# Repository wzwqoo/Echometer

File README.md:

# Echometer

A pocket-sized, battery-powered **ultrasonic bat detector**. It listens for
bat calls above 19 kHz, and when it hears one it records a 3.84-second
full-spectrum clip at **256 ksps** into PSRAM and serves it over its own Wi-Fi
network. Open a phone browser, download the WAV, and import it straight into
the Wildlife Acoustics **Echo Meter** app — the files carry GUANO metadata and
are accepted as Echo Meter Touch 2 Pro recordings.

No SD card, no cables, no custom phone app, no laptop in a field at midnight.

This is **v4**, the fourth board in the series. It is the first one that is
genuinely portable and the first one that doesn't clip on a close bat: the
analog front end has **six switchable gain steps from 22× to 782×**, chosen
from the web page or tracked automatically, and the whole thing runs off a
protected LiPo with charger and boost on board. See
[Design history](#design-history) for how it got here.

|  |  |
|:--:|:--:|
|  |  |
| **Japanese Pipistrelle**<br>*Alionoctula abramus* &mdash; recorded by this board, opened in the Echo Meter app | **Least Horseshoe Bat**<br>*Rhinolophus pusillus* &mdash; the ~108 kHz caller that set the sample rate |

---

## Contents

- [Specifications](#specifications)
- [How it works](#how-it-works)
- [Repository layout](#repository-layout)
- [Getting started](#getting-started)
- [Using it](#using-it)
- [Hardware in brief](#hardware-in-brief)
  - [Switchable gain](#switchable-gain)
  - [Power](#power)
  - [Pinout](#pinout)
- [Firmware in brief](#firmware-in-brief)
- [Errata — read before ordering the PCB](#errata--read-before-ordering-the-pcb)
- [Design history](#design-history)
- [Roadmap](#roadmap)
- [References](#references)

---

## Specifications

| | |
|---|---|
| Detection band | 19 – 128 kHz |
| Sampling | 256 ksps, 12-bit, external SAR ADC (ADCS7476) |
| Frequency resolution | 125 Hz/bin (2048-point FFT, 8 ms frames) |
| Analog gain | 6 steps, **22× – 782×** (26.9 – 57.9 dB), manual or AGC |
| Microphone | Knowles SPU0410LR5H-QB MEMS, −38 dBV/Pa, usable to ≈ 80 kHz |
| Clip length | 3.84 s (983 040 samples, 1.97 MB) |
| Clip storage | up to 8 PSRAM slots — 4 on an 8 MB module; RAM-only, lost at power-off |
| Transfer | open Wi-Fi AP `echometer` → `http://192.168.4.1` |
| File format | 16-bit mono WAV + GUANO chunk, `CHIRP_YYYYMMDD_HHMMSS.wav` |
| Compute | ESP32-S3 DevKitC-1, octal PSRAM, ESP-IDF ≥ 5.2 |
| Power | 2000 mAh LiPo, TP4056 charger @ 1 A, DW01/FS8205A protection, MT3608 boost |
| PCB | 4-layer, KiCad 10, gerbers in [`hardware/fab/`](hardware/fab/) |

## How it works

```text
                        ┌── 74HC4053 mux ──┐
                        │  (3 × GPIO)      │
                        ▼                  ▼
  ┌────────┐      ┌───────────┐      ┌──────────┐      ┌───────────┐
  │ conical│      │  OPA838   │      │  TL972   │      │ ADCS7476  │
──│  horn  │─────▶│  ×4.25/34 │─────▶│ ×5.2…23  │─────▶│ 12-bit    │
  │        │ MEMS │  stage 1  │  HP  │ stage 2  │  AA  │ 256 ksps  │
  └────────┘  mic └───────────┘      └──────────┘      └─────┬─────┘
                                                             │ I²S RX DMA
                                                             ▼
   Safari ◀── HTTP ◀── SoftAP ◀── PSRAM clip ◀── trigger ◀── 2048-pt FFT
     │                             4 × 3.84 s      >19 kHz    (esp-dsp)
     ▼                                             narrowband
  Echo Meter app                                   3 frames
```

1. Press **BOOT** to arm. The LED flashes green whenever ultrasound is present.
2. Every 2048-sample buffer is FFT'd. A detection needs a **narrowband** peak
   above 19 kHz that **persists** across 3 consecutive frames — broadband
   transients (a finger on the board, contact noise) are rejected.
3. On detection the clip streams into a PSRAM slot for 3.84 s. The LED goes
   completely silent during the write — its own drive current used to print
   evenly-spaced clicks into the spectrogram.
4. Blue flash when saved, then back to idle. Join Wi-Fi `echometer`, browse to
   `http://192.168.4.1`, download or delete clips, and set the gain.

The interesting trick is the ADC clocking. The ESP32-S3's internal ADC-DMA path
tops out near 83 ksps, nowhere near enough for a bat. So an external SAR ADC is
driven by the **I²S peripheral pretending to be an SPI master**: in 16-bit
stereo master mode the WS line toggles every 16 bit-clocks, so WS becomes the
ADC's `CS#` and BCK its `SCLK`. RX DMA captures every sample with zero
per-sample CPU, jitter-free, at an 8.192 MHz bit clock.

## Repository layout

| Path | Contents |
|---|---|
| [`hardware/`](hardware/) | KiCad 10 project — schematic, 4-layer PCB, gerbers, BOM, horn generator. See [hardware/README.md](hardware/README.md) for the analog design. |
| [`firmware/`](firmware/) | ESP-IDF application. See [firmware/README.md](firmware/README.md) for the detection logic and bring-up lessons. |
| [`firmware/main/archive/`](firmware/main/archive/) | Earlier firmware variants kept for reference — v3's original, an SD-card recorder, a board bring-up test. |
| [`docs/img/`](docs/img/) | Photographs and screenshots used in this README. |

## Getting started

**You need:** an ESP32-S3-DevKitC-1 with **octal** PSRAM, the assembled v4
board, a 2000 mAh LiPo with a JST-PH lead, and ESP-IDF ≥ 5.2.

```bash
cd firmware
. ~/software/esp-idf/export.sh              # adjust to your ESP-IDF path
idf.py build
idf.py -p /dev/ttyUSB0 flash monitor        # the COM (UART) USB-C port
```

The DevKitC-1 has two USB-C ports. **COM** (CP2102N → UART0) does flashing and
the log console and always works. If a bad flash ever bricks the app: hold
BOOT, tap RESET, release → ROM download mode, reflash over COM.

Before you build the board, read
[Errata](#errata--read-before-ordering-the-pcb) — item 1 is blocking.

## Using it

| Action | What happens |
|---|---|
| Press BOOT | Arm. LED flashes green while ultrasound is present. |
| Detection | LED silent, 3.84 s clip written to PSRAM, then blue flash. |
| Press BOOT while armed | Disarm back to idle. Presses during a write are ignored. |
| Join `echometer` (open network) | AP is up in every state. |
| `http://192.168.4.1` | Clip list, newest first: download, delete, set gain, toggle AGC. |

Clips live in RAM only — **they are lost at power-off**. Download before you
disconnect the battery.

To get a clip into the Echo Meter app on iOS: download in Safari, then
Files → share sheet → *Copy to Echo Meter*.

---

## Hardware in brief

Everything below is the summary. Full derivations — op-amp selection, mic
specs, the input common-mode budget, every filter corner, the power design,
the pinout, the acoustic horn and the bat call-level budgets — are in
[hardware/README.md](hardware/README.md).

Single channel, single 3.3 V analog rail, everything biased to mid-rail
(VREF ≈ 1.65 V). Stage 1 is a **TI OPA838** — 300 MHz GBW, decompensated,
1.8 nV/√Hz — because gain × 120 kHz has to fit inside the gain-bandwidth
product. Stage 2 is a **TI TL972**, rail-to-rail in and out, which drives the
ADC to full swing on 3.3 V. Both stages are non-inverting with a 1 kΩ leg to
VREF. The band is ≈ 19 kHz – 128 kHz: two 10 nF high-passes stacked at the
bottom, a 72 kHz RC anti-alias filter ahead of the ADC at the top.

### Switchable gain

A **74HC4053** analog mux switches extra feedback resistors **in parallel**
with a permanent one at each stage's summing node — one switch on stage 1, two
on stage 2. Parallel resistors *lower* the gain, the permanent resistors mean
the loop is never open, and the mux's Y0-when-LOW polarity means the state the
ESP32's GPIOs sit in at reset is **minimum gain, which cannot clip**.

| **Total** | dB | Clips near | Use |
|---|---|---|---|
| **22×** | 26.9 | 105 dB SPL | cave / roost, bats at arm's length |
| **51×** | 34.2 | 98 dB SPL | |
| **98×** | 39.8 | 92 dB SPL | general close work |
| **210×** | 46.4 | 86 dB SPL | default at cold boot |
| **408×** | 52.2 | 80 dB SPL | |
| **782×** | 57.9 | 74 dB SPL | distant passes, ~30 m |

Steps are 5.6–7.3 dB apart. "Clips near" is the input SPL at which the TL972
output hits its rail. The range stops at 782× because past ~800× you are
amplifying the microphone's own noise rather than signal — further reach has to
come from narrowband processing, not from the front end.

Resistor values, the switch-state table, why the three switches are split 1/2
across the stages, and why the switches sit at the summing node:
[hardware/README.md](hardware/README.md#gain--how-the-switching-works).

### Power

USB charger → cell → protection → boost to 5.31 V for the module, with the
analog rail taken off separately. The one decision worth naming here: **the
analog LDO is fed from the battery, not from the boost.** The TPS74801's
separate BIAS pin runs its control loop from +5 V so the pass FET can be driven
above VIN, which lets IN sit at the raw cell voltage. The win isn't efficiency,
it's noise — the analog rail never sees the MT3608's 1.2 MHz ripple, which no
LDO's PSRR is good at rejecting.

Two things to know before you use it:

- **Charging while running works**, but the load current means the TP4056 may
  never reach its termination threshold, so it can sit in CV at 4.2 V and the
  green LED may never come on. Don't leave it plugged in for days.
- **There is no power switch.** The board runs from the moment the cell is
  connected — unplug J6 to stop it. See errata 5 to store it charged.

Rail diagram, component values, the 5.31 V boost-margin calculation and where
to add a switch if you want one: [hardware/README.md](hardware/README.md#power).

### Pinout

ADC on GPIO 4 / 5 / 6 (I²S WS / BCK / DIN), gain select on GPIO 38 / 37 / 36
(⚠ **see errata 1**), RGB LED on 48, BOOT button on 0. Full header-pin table:
[hardware/README.md](hardware/README.md#pinout--esp32-s3-devkitc-1).

---

## Firmware in brief

ESP-IDF application, single `main.c`. Full detail — state machine, WAV/GUANO
construction, sdkconfig requirements and the bring-up lessons — is in
[firmware/README.md](firmware/README.md).

| State | Entered by | LED |
|---|---|---|
| IDLE | boot / disarm | off |
| DETECT | BOOT press | green flash while ultrasound present |
| RECORD | detection persists 3 frames | **silent** for the 3.84 s write |
| after RECORD | write finished | blue flash ~1.2 s → IDLE |

**Detection.** 2048-point real FFT per buffer via esp-dsp. Trigger requires, on
3 consecutive buffers: a bin above 19 kHz (bin ≥ 152) over
`ULTRASONIC_THRESH_COUNTS`, **and** a peak ≥ 20× the average power of the rest
of the >19 kHz band. The tonality test is what rejects broadband impulses; the
persistence test is what rejects momentary ones.

**Gain control.**

- **Web:** `http://192.168.4.1` → tap a gain. Picking one by hand turns the AGC
  off, and the choice is saved to NVS so it survives a power cycle.
- **AGC:** fast attack, slow decay. Any frame peaking above 90 % of full scale
  drops the gain one step immediately; the gain only steps back up after ~1 s
  (120 frames) below 10 %. Asymmetric on purpose — clipping happens in the
  **analog** domain before the ADC, so a clipped call is unrecoverable, while a
  symmetric AGC would pump on every gap between calls.
- **Frozen during RECORD.** A gain step mid-clip would put a discontinuity in
  the waveform and make the clip useless for absolute amplitude. The gain in
  force is latched at trigger time and written into the clip's GUANO metadata
  (`Note` plus `Echometer|Gain`), so SPL can be reconstructed offline.
- After every gain change the detector skips 2 frames while the mux's charge
  injection settles out of the summing node, so a switch is never mistaken for
  a call.

**HTTP endpoints:** `/` (clip list), `/dl`, `/del`, `/gain?i=N`, `/agc?on=0|1`.

**A note on the device identity in the metadata.** The Echo Meter app validates
the GUANO `Model` field against known Wildlife Acoustics modules and rejects
anything else, so the firmware writes `Model: Echo Meter Touch 2 Pro` — a
format this recorder genuinely matches (256 kHz, 16-bit, full-spectrum mono).
True provenance is kept in the GUANO `Note` field. Keep that in mind before
sharing files anywhere that trusts the device tag.

---

## Errata — read before ordering the PCB

Known problems with the v4 board as drawn. **Item 1 is blocking** — fix it in
the schematic before you send gerbers. The rest are things to know before you
build, not stop-ships.

**1. Two gain-select signals land on the octal-PSRAM bus.** With
`CONFIG_SPIRAM_MODE_OCT=y`, GPIO35/36/37 belong to the PSRAM controller and
cannot be used for anything else, but the PCB routes Gain S2 to J12.11
(GPIO37) and Gain S3 to J12.12 (GPIO36). The firmware already assumes the
corrected pins — `PIN_GAIN_S1/S2/S3` are GPIO 38/39/40 — so an uncorrected
board will not switch gain.
**Fix:** move S2 to J12.9 (GPIO39) and S3 to J12.8 (GPIO40). GPIO39/40 are
MTCK/MTDO, free here only because the DevKitC-1 debugs over the built-in
USB-Serial-JTAG on GPIO19/20. See
[firmware/README.md](firmware/README.md#5-gpio-choice-is-constrained-by-psram-mode).

**2. Stage 1's lowest gain step sits below the OPA838's minimum stable gain.**
The OPA838 is decompensated, with a minimum stable gain of +7; stage 1's low
setting is 4.25. The design relies on C14 (27 pF across R13) to provide the
compensation the topology needs, and 27 pF is small enough that stray
capacitance matters. If the three low gain steps ring, peak or oscillate,
this is the first place to look.

**3. The +5 V rail has ~390 mV of bias margin, and it needs verifying.** The
boost is set to 5.31 V because the TPS74801's BIAS pin must stay at least
1.62 V above the 3.3 V output, i.e. ≥ 4.92 V. Measure the sag on a real board:
if +5 V dips below 4.92 V during a Wi-Fi TX burst, the LDO loses bias headroom
and the analog rail glitches during exactly the moments you transmit.

**4. The SD footprint (J5) is +5 V and unbuffered.** Pin 5 is fed +5 V and the
SPI lines are not level-shifted, so J5 accepts an SD **module** with its own
regulator and level shifters — never a bare card socket. The current firmware
does not use it; leave it unpopulated unless you are building the archived
recorder.

**5. There is no power switch, and the cell will over-discharge in storage.**
The boost's EN is tied to its own input, so the board runs from the moment the
cell is connected. Standby drain as built is 50–120 mA, which flattens
2000 mAh in 17–40 hours and then parks the cell at the DW01's 2.4 V cutoff —
bad for lithium.
**Fix:** unplug J6 for storage and store the cell charged. If you add a switch,
put it in the `Lipo+ → L1 / U8.5` branch, **not** on the boost's EN pin — the
MT3608 is asynchronous, so `Lipo+ → L1 → D3 → +5V` is a permanent DC path that
survives disabling the boost. See
[hardware/README.md](hardware/README.md#charging-and-switching-both-with-caveats).

**6. Several schematic symbols carry stale part numbers.** R13, R23/R25, R24
and R26 inherit a 24 kΩ `Part#` / `LCSC Part #` from their previous value, and
C16 inherits a 10 nF one. Those fields are cleared in the checked-in
[`hardware/v4.csv`](hardware/v4.csv), so **ordering from the CSV is safe** —
but fix the symbol properties before the next `kicad-cli sch export bom`.

---

## Design history

Four boards, each one built to answer the question the previous one raised.

| | v1 | v2 | v3 | v4 |
|---|---|---|---|---|
| **Compute** | STM32F401CBU6 | STM32F446RET6 (Nucleo) | ESP32-S3 | ESP32-S3 |
| **Sampling** | internal ADC, free-running DMA | internal ADC, TIM2-gated **240 ksps** | external ADCS7476 via I²S, **256 ksps** | same |
| **Detection** | none — raw recorder | CMSIS-DSP FFT, >19 kHz threshold | + tonality + persistence | same |
| **Storage** | micro-SD (SPI1, FatFS) | micro-SD (SPI3, FatFS) | 4 × PSRAM slots | up to 8 slots |
| **Retrieval** | pull the card / USB CDC | pull the card / UART + Python | **Wi-Fi + Safari + GUANO WAV** | same |
| **Gain** | analog board, fixed | fixed 121× | fixed 625× | **6 steps, 22×–782× + AGC** |
| **Listening** | heterodyne + FD to a speaker | — | — | — |
| **Power** | 9 V in, LM2574 + LDOs | dev-board USB | USB (browned out) | **LiPo + charger + protection + boost** |

### v1 — does the analog even work?

A custom STM32F401CBU6 mainboard plus a separate analog board carrying the
classic hobbyist bat-detector chain: SPU0410 MEMS mic → LM358 preamp → CD4066
mixer switched by a TLC555 → LM386 → speaker, i.e. **heterodyne and frequency
division straight to your ears**. Two small preamp boards (one OPA838, one
TL972) were spun alongside it to compare op-amps on real signals.

The MCU side ran FreeRTOS with three tasks: ADC1 in continuous DMA into a
double buffer, a ring buffer feeding FatFS on a micro-SD over SPI1, and a
debounced button. Power was 9 V in through an LM2574 buck and NCP718/NCP163
LDOs.

**What it proved:** the microphone, the horn and the amplifier chain all work,
and you can hear bats. **What it cost:** hearing a bat isn't recording one —
the heterodyne path destroys the signal it demodulates. There was no detection
logic at all, so recording was start/stop by hand. The ADC free-ran on a
software start with no timer trigger, so the sample clock had jitter. And
splitting analog and digital across two boards joined by 4-pin headers was an
invitation to pickup.

**→ v2:** drop the speaker path entirely, go full-spectrum digital, put the ADC
on a hardware time base, and add a real FFT detector.

### v2 — detect it, don't just hear it

A Nucleo-F446RE with a custom analog + SD daughterboard: SPU0410 →
**OPA838 → TL972**, single 3.3 V rail, mid-rail bias — the two-stage topology
that survives into v4. TIM2 TRGO gates ADC1 at exactly **240 ksps** into a
2 × 2048 DMA double buffer, and each half-buffer goes through
`arm_rfft_fast_f32` from CMSIS-DSP: 117 Hz/bin, trigger on any bin ≥ 163
(>19 kHz) above 50 counts. Detect and record are two states with different LED
blink rates; recording writes raw `uint16` samples to FatFS over SPI3 with an
`f_sync` every 100 writes. Python tools (`bat_record.py`, `bat_viewer.py`,
`bat_waveform.py`) pull captures over the serial port and plot them.

Gain went from 11× per stage (**121×** total) to 25× per stage (**625×**)
during bring-up. At 121× real calls sat barely above the noise floor; the 5×
jump is what moved detection from marginal to reliable.

**What it cost:** 240 ksps means a 120 kHz Nyquist, and that was the internal
ADC's practical ceiling — the target species here, *Rhinolophus pusillus*, calls
at ~108 kHz, right at the edge. Getting files off meant pulling the card or
dumping over serial. And the gain was still a soldered constant.

**→ v3:** an external ADC fast enough to have real margin above 108 kHz, and a
way to get files onto a phone in the field.

### v3 — fast enough, and wireless

ESP32-S3 with an external **ADCS7476** 12-bit SAR clocked by the I²S
"WS-as-CS" trick at **256 ksps** — zero per-sample CPU, 128 kHz Nyquist.
Detection moved to esp-dsp and gained the two tests that make it usable
outdoors: **tonality** (peak bin ≥ 20× the mean power of the rest of the band)
and **persistence** (3 consecutive frames). Clips go to PSRAM — four 3.84 s
slots in 8 MB — and are served over a SoftAP as WAVs with a **GUANO** metadata
chunk that the Echo Meter iPhone app accepts. Two mics and two full channels,
fixed 625×.

That combination is what made it a real detector: no card, no cable, and a
phone app that already knows how to draw a spectrogram.

**What it cost, and this is the whole reason v4 exists:**

- **625× clipped constantly.** Roughly 9 out of 10 close calls railed the
  second stage, smearing the spectrogram into broadband bars and false
  harmonics. Clipping happens in the analog domain, so no amount of digital
  processing recovers it — and there was no way to turn the gain down.
- **It browned out.** Wi-Fi RF calibration and TX bursts (300–400 mA on top of
  octal PSRAM) tripped the brownout detector on marginal USB supplies. Inline
  USB "noise filter" dongles made it *worse* — series resistance is exactly the
  problem. Downloads, being the heaviest sustained RF load, failed first.
- **A floating ADC input false-triggered on touch.** Fixed in firmware by the
  tonality and persistence tests; the hardware fix was left for the next spin.
- **The LED printed clicks into the spectrogram.** The WS2812's RMT refresh
  coupled into the front end, so the firmware learned to keep it silent for the
  whole capture window.
- **The mic-supply filter did nothing.** 10 Ω + 110 nF corners at 159 kHz —
  above the band it was supposed to clean.

**→ v4:** make the gain adjustable, and stop feeding a 400 mA radio through a
thin cable.

### v4 — portable, and it doesn't clip

| Area | v3 | v4 |
|---|---|---|
| Gain | fixed 625× | **6 steps, 22×–782×**, web-selectable + AGC |
| Gain control | — | 74HC4053 mux at both summing nodes, 3 GPIOs |
| Channels | 2 mics, 2× OPA838 + 2× TL972 | 1 mic, 1× OPA838 + 1× TL972 — gain replaces the second channel |
| Power source | USB only | LiPo 2000 mAh + charger + protection + boost |
| Charging | — | TP4056 @ 1 A, red/green status LEDs |
| Cell protection | — | DW01 + FS8205A, low-side |
| 3V3 analog rail | LDO from 5 V (boost output) | LDO **from the battery**, bias from 5 V |
| Mic supply filter | 10 Ω + 110 nF (159 kHz — did nothing) | **100 Ω + 10 µF (159 Hz)** |
| Anti-alias | 100 Ω + 10 nF (159 kHz, above Nyquist) | **100 Ω + 22 nF (72 kHz)** |
| Wi-Fi burst reservoir | external | **470 µF on board** at the module header |
| Floating ADC input | v3 erratum — false triggers | driven from the op amp through 100 Ω; can't float |
| Clip metadata | timestamp only | **gain recorded in GUANO** |

The trade worth naming: v4 gives up v3's second channel. Two mics at two fixed
gains is the other classic way to get wide dynamic range — digitise both, keep
whichever didn't clip, zero AGC artifacts. One switched channel costs a mux and
some AGC logic but buys 31 dB of range instead of one fixed step, and it frees
the board area that paid for the battery.

## Roadmap

Carried forward, in rough order of value:

- **Ring buffer for pre-trigger audio.** The clip currently starts at the
  triggering buffer, so the calls *before* detection fired are lost. This is
  the single biggest capture upgrade left — every serious passive recorder
  keeps a few seconds of pre-roll.
- **Adaptive trigger.** A running noise-floor estimate (exponential moving
  average of ultrasonic-band energy) rather than the fixed
  `ULTRASONIC_THRESH_COUNTS`. Note that with variable gain a fixed threshold
  now means a *different* absolute sensitivity at each step, which makes this
  more pressing than it was in v3.
- **Call-shape gating.** Require a swept FM component, plausible duration
  (~2–20 ms) and inter-pulse interval, to reject bush-crickets and machinery.
  The tonality + persistence test is a first cut at this.
- **Duty cycling** for unattended overnight runs — light sleep between checks,
  or a low-power always-on trigger path that wakes full recording on a hit.
- **Pause the AP during capture**, so no TX spike or RF pickup can coincide
  with the 3.84 s sampling window.

For reference, AudioMoth uses a plain amplitude threshold; Song Meter /
Kaleidoscope use band-limited energy triggers; Anabat uses zero-crossing
frequency division; and the most advanced run an on-device CNN
(e.g. BatDetect2) to detect and classify in real time.

## References

- [GUANO metadata specification](https://guano-md.org)
- TI [OPA838](https://www.ti.com/lit/gpn/opa838), TL972, ADCS7476, TPS74801 datasheets
- Knowles SPU0410LR5H-QB datasheet and Ultrasonic Application Note AN17
- [AudioMoth](https://www.openacousticdevices.info/) — reference low-power design
- [BatDetect2](https://github.com/macaodha/batdetect2) — CNN call detection and classification

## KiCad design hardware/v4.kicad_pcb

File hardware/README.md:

# Hardware — analog front end, power, PCB and acoustics

KiCad 10 project (`v4.kicad_pro`, schematic + 4-layer PCB), fabrication outputs
in [`fab/`](fab/), BOM in [`v4.csv`](v4.csv), and the parametric acoustic-horn
generator [`ultrasonic_horn_freecad.py`](ultrasonic_horn_freecad.py).

The schematic is split over two sheets: `v4.kicad_sch` (root) and
`MCU.kicad_sch` (everything — front end, ADC, power, module headers).

> Read the errata in the [top-level README](../README.md#errata--read-before-ordering-the-pcb)
> before ordering. Item 1 is blocking: two of the three gain-select signals land
> on the octal-PSRAM bus and must be moved.

---

## Analog front end

### Transducer

**Knowles SPU0410LR5H-QB**, one fitted. An analog MEMS mic with usable response
through the target bat band; its raw output is small — tens of millivolts for a
loud, close call — so it must be amplified and biased into the ADC's input
range before sampling.

| Parameter | Value |
|---|---|
| Type | analog MEMS (SiSonic), bottom-port, omnidirectional |
| Sensitivity | −38 dBV/Pa (±3 dB) ≈ 12.6 mV/Pa @ 94 dB SPL, 1 kHz |
| SNR | 63 dB(A) → self-noise ≈ 31 dB(A) SPL |
| Frequency response | ~100 Hz → usable to ≈ 80 kHz (rising resonance ~20–25 kHz) |
| Max acoustic input | ≈ 120 dB SPL |
| Supply / current | 1.5–3.6 V / ~123 µA |
| Output impedance | ~200 Ω |
| Package | 3.76 × 2.95 × 1.10 mm, 0.25 mm port |

The 0.25 mm acoustic port sits at the throat of the conical horn.

### Op-amp choice

The amplifier must pass the full ultrasonic band **and** apply large gain
without rolling off, which sets a hard requirement on gain–bandwidth product:
`GBW ≥ gain × 120 kHz`. Two devices:

| Stage | Part | Why |
|---|---|---|
| 1st gain | **TI OPA838** (OPA838IDBVR) | 300 MHz GBW, decompensated (min stable gain +7), 1.8 nV/√Hz, ~1 mA |
| 2nd gain / ADC driver | **TI TL972** (TL972IDR) | dual rail-to-rail I/O, 12 MHz GBW — drives the ADC to full swing on 3.3 V |

Both run single-supply and bias the signal to **mid-rail (VREF ≈ 1.65 V)** so
the AC waveform swings symmetrically inside the ADC's 0–3.3 V window. A **TI
TPS74801** low-noise LDO supplies the analog rail and VREF, so digital
switching noise doesn't couple into the µV-level mic signal.

Note the OPA838's decompensation: its minimum stable gain is +7, which is a
real constraint on the gain-step table below — stage 1's low setting of 4.25
would be unstable on its own, and is only usable because C14 (27 pF across
R13) provides the compensation the topology needs.

### Gain — how the switching works

Both stages are non-inverting with a 1 kΩ leg to VREF. Each has a
**permanent** feedback resistor, and a **74HC4053** analog mux switches further
resistors in **parallel** with it, which *lowers* the gain.

| Stage | Amp | Rg | Permanent Rf | Switched in parallel | Gains |
|---|---|---|---|---|---|
| 1 | OPA838 (U3) | R6 = 1 k | R13 = 33 k | R26 = 3k6 via switch 1 | 34 / 4.25 |
| 2 | TL972B (U2) | R12 = 1 k | R25 = 22 k | R23 = 22 k (sw 2), R24 = 6k8 (sw 3) | 23 / 12 / 6.2 / 5.2 |

Three design decisions are load-bearing here:

**The permanent resistors are never switched out.** The loop is closed in every
mux state, including the ~300 ms before firmware runs and the instant the mux
transitions. Nothing can rail.

**The polarity is chosen so reset means quiet.** The 4053 selects Y0 — resistor
connected, parallel combination, *lower* gain — when its select pin is **LOW**.
GPIOs sit low at reset, so the board wakes at minimum gain, which cannot clip.

**The switches sit at the summing node**, mux common to the op-amp inverting
input and the resistors to Y0. Both sides of a closed switch are therefore at
virtual ground, so the mux's on-resistance sees an almost constant voltage.
That is what keeps the 4053's on-resistance nonlinearity out of the signal —
put the switch anywhere the voltage swings and it becomes a distortion source.

**Why the switches are split 1 / 2 across the stages.** Switching resistors in
parallel adds conductances, so the achievable ratio within one stage is bounded
— a single stage can only span about 18 dB however you pick the values. Two
stages multiply, giving the full 31 dB.

### The six steps

| S1 | S2 | S3 | Stage 1 | Stage 2 | **Total** | dB | Clips near |
|---|---|---|---|---|---|---|---|
| 0 | 0 | 0 | 4.25 | 5.2 | **22×** | 26.9 | 105 dB SPL |
| 0 | 0 | 1 | 4.25 | 12 | **51×** | 34.2 | 98 dB SPL |
| 0 | 1 | 1 | 4.25 | 23 | **98×** | 39.8 | 92 dB SPL |
| 1 | 1 | 0 | 34 | 6.2 | **210×** | 46.4 | 86 dB SPL |
| 1 | 0 | 1 | 34 | 12 | **408×** | 52.2 | 80 dB SPL |
| 1 | 1 | 1 | 34 | 23 | **782×** | 57.9 | 74 dB SPL |

Steps are 5.6–7.3 dB apart. "Clips near" is the input SPL at which the TL972
output hits its rail, for the SPU0410 at −38 dBV/Pa with ~1.45 V of peak swing.

Three switches give 8 states, not 6. The two omitted (177× and 26×) sit within
1.5 dB of a neighbour, and that bunching is unavoidable: the four states of two
parallel switches always satisfy `G(both) = G(a) + G(b) − G(neither)`, so they
cannot be spaced evenly.

### Input common-mode headroom — checked, and why VREF must stay mid-rail

Neither amp has a rail-to-rail *input* stage, and both stages are
non-inverting, so the + input carries signal rather than sitting still. On a
3.3 V rail:

| | Spec | Window on 3.3 V | Worst-case swing here | Margin |
|---|---|---|---|---|
| TL972 (U2) | V<sub>ICM</sub> = VCC− + 1.15 … VCC+ − 1.15 | **1.15 – 2.15 V** | 1.371 – 1.929 V (at A2 = 5.2) | 221 mV |
| OPA838 (U3) | VS− − 0 … VS+ − 1.3 (over temp) | **0 – 2.00 V** | 1.584 – 1.716 V | 284 mV |

Both pass. The TL972's is the tighter one and it appears at the *lowest* gain
step, where the output is clipping at ±1.45 V and its + input therefore has to
swing ±279 mV. The OPA838 is never stressed because its + input only ever
carries the mic-level signal, at most ±66 mV — the mic itself runs out
(AOP ≈ 120 dB SPL) at about the same point its 2.0 V ceiling would be reached.

The useful consequence: the safe window is the **intersection**, 1.15 – 2.00 V,
and VREF at 1.65 V sits near its centre. Do not "improve" headroom by moving
VREF down — 1.15 V is a hard floor for the TL972, and anything below ~1.4 V
starts eating the margin you gained at the top.

### Why the gain stops at 782×

The SPU0410's own noise integrated over 20–120 kHz is around **38 dB SPL**, and
a bat at 30 m arrives at roughly 30 dB SPL. Past ~800× you are amplifying mic
noise, not signal.

v3's jump from 121× to 625× helped because at 121× the ADC's LSB was still
competing with the mic noise; at 782× the mic dominates and more gain buys
nothing. Further range has to come from narrowband processing — FFT bin energy,
matched filter — not from the front end.

### Filtering — ultrasonic only

| Element | Value | Corner | Purpose |
|---|---|---|---|
| C12 + (R3 + mic Zout ≈ 1.3 k) | 10 nF | 12.2 kHz | HP, mic → stage 1 |
| C13 + (R15 + R10 ≈ 1.1 k) | 10 nF | 14.5 kHz | HP, stage 1 → stage 2 |
| *both together* | | **≈ 19 kHz −3 dB** | −33 dB at 2 kHz |
| C14 across R13 | 27 pF | 179 kHz | stage-1 LP / compensation |
| C15 across R25 | 27 pF | 268 kHz | stage-2 LP / compensation |
| R17 + C16 | 100 Ω + 22 nF | 72 kHz | anti-alias ahead of the ADC |
| R18 + C19 | 100 Ω + 10 µF | 159 Hz | mic **supply** filter (not signal) |

Two of these look similar and do opposite jobs, and v3 got one of them wrong.
R18/C19 is a **power-supply** filter on the mic's VDD pin — it wants its corner
far *below* the band, and 159 Hz gives about 48 dB of rejection at 40 kHz.
v3 used 10 Ω + 110 nF, which corners at 159 kHz and therefore did essentially
nothing. C12/C13 are the **signal** high-pass and want their corners *at* the
band edge.

The anti-alias filter had the same class of bug in v3: 100 Ω + 10 nF corners at
159 kHz, above the 128 kHz Nyquist, so it wasn't anti-aliasing anything. 22 nF
brings it to 72 kHz.

Keeping R6/R12 at 1 kΩ is what let both 27 pF compensation caps stay. Scaling
the network up 10× for resistor accuracy would have demanded ~2 pF caps, which
are not buildable against stray capacitance. Mux on-resistance instead adds
1.5 % error at the 33 k tap and 4 % at the 6k8 tap — irrelevant for a detector.

---

## Digital acquisition

Sampling is done by an **external 12-bit SAR ADC (ADCS7476, rated 1 MSPS)** run
at **256 ksps → 128 kHz Nyquist**, covering the full bat band. The ESP32-S3's
built-in ADC-DMA path tops out near 83 ksps — far too slow — so the external
ADC is clocked with a hardware trick:

- The **I²S peripheral** runs as master, 16-bit **stereo**, so its **WS line
  toggles every 16 bit-clocks**.
- **WS → ADC CS**, **BCK → SCLK**, **SDATA → I²S DIN**. WS-low frames each
  conversion (16 clocks readout); WS-high is the re-track gap.
- I²S RX DMA captures every sample jitter-free with **zero per-sample CPU**.
  At 256 ksps the bit clock is `256000 × 2 × 16 = 8.192 MHz`.

Buffers of **2048 samples** (one FFT frame, 8 ms) feed the detector —
125 Hz/bin resolution; the detection band starts at bin 152 (19 kHz). See
[../firmware/README.md](../firmware/README.md) for the detection logic and the
bit-alignment quirk in the returned word.

The ADC input is driven from the TL972 output through R17 (100 Ω), so unlike
v3 it can never float. A floating ADC input is an antenna, and touching it
false-triggered v3's detector every time.

### Signal levels & detection budget

| Quantity | Value |
|---|---|
| ADC | 12-bit, full scale 4095 counts over 3.3 V |
| Bias point | VREF ≈ 1.65 V |
| Raw transducer signal (close call) | ~33–50 mV |
| Gain range | 22× – 782×, six steps |
| Detection band | > 19 kHz |
| Known interferer | ~50 kHz USB switching noise falls **inside** the band |

The FFT detection threshold (`ULTRASONIC_THRESH_COUNTS`) sits a few dB above
the *amplified* noise floor. Because the gain is now variable, that fixed
count threshold represents a different absolute sensitivity at each step — see
the roadmap note about an adaptive trigger.

---

## Power

```text
USB ──▶ TP4056 ──▶ [cell] ──▶ DW01/FS8205 ──▶ Lipo+ ─┬─▶ MT3608 ──▶ +5V ──▶ ESP32 module
                                                     │              └──▶ TPS74801 BIAS
                                                     └──────────────────▶ TPS74801 IN ──▶ +3V3 analog
```

| Block | Part | Setting |
|---|---|---|
| Charger | TP4056 (U5) | R7 = 1.2 k → **1 A** (0.5 C into 2000 mAh); thermal pad on GND |
| Protection | DW01 (U6) + FS8205A (U7) | low-side, R20 100 Ω + C25 100 nF, R8 1 k on CS |
| Boost | MT3608 (U8) | L1 4.7 µH, D3 SS34, R21 150 k / R22 19.1 k → **5.31 V** |
| Analog LDO | TPS74801 (U10) | IN from Lipo+, BIAS + EN from +5 V, R11 31.2 k / R9 10 k → **3.30 V** |
| Wi-Fi reservoir | C28 470 µF | at the module header |
| Status | D1 red / D2 green | TP4056 CHRG / STDBY |

### The LDO is fed from the battery, not from the boost

That is the whole point of the TPS74801's separate BIAS pin. BIAS runs the
control loop and the gate driver, so the pass FET can be driven *above* VIN.
That lets IN sit at the raw cell voltage (3.0–4.2 V) and drop only ~50 mV at
the ~25 mA the analog side draws.

The win isn't efficiency — it's noise. Routed the obvious way (LDO fed from the
boost output), the analog rail inherits the MT3608's 1.2 MHz switching ripple,
and no LDO's PSRR is good at 1.2 MHz. Feeding it from the cell means the analog
rail never sees the switcher at all.

**Boost output is 5.31 V, not 5.0 V, and that is deliberate.** BIAS must stay
at least 1.62 V above the 3.3 V output, i.e. ≥ 4.92 V. At 5.1 V there was only
180 mV of margin — about what a Wi-Fi TX burst eats. Measure the sag on a real
board; if +5 V dips below 4.92 V during TX, the LDO loses bias headroom and the
analog rail glitches during exactly the moments you transmit.

### Charging and switching, both with caveats

**Charging while running works** — the cell buffers everything — but the load
current means the TP4056 may never see its termination threshold. It can sit in
CV at 4.2 V indefinitely and the green LED may never come on. Don't leave it
plugged in for days.

**There is no power switch.** The boost's EN is tied to its own input, so the
board runs from the moment the cell is connected; unplug J6 to stop it. Standby
drain as built is 50–120 mA, which flattens 2000 mAh in 17–40 hours and then
parks the cell at the DW01's 2.4 V cutoff — bad for storage.

If you add a switch, put it in the **`Lipo+ → L1 / U8.5` branch**, not on the
boost's EN pin. The MT3608 is asynchronous, so `Lipo+ → L1 → D3 → +5V` is a
permanent DC path: disabling the boost leaves the module's regulator powered
anyway. Breaking the boost input kills that path and still leaves the charger
connected.

---

## Pinout — ESP32-S3 DevKitC-1

| Function | Header pin | GPIO |
|---|---|---|
| ADC CS (I²S WS) | J11.4 | 4 |
| ADC SCLK (I²S BCK) | J11.5 | 5 |
| ADC SDATA (I²S DIN) | J11.6 | 6 |
| SD nCS / MOSI / SCK / MISO | J11.16–19 | 10 / 11 / 12 / 13 |
| +5 V / GND | J11.21 / J11.22 | — |
| Gain S1 | J12.10 | 38 |
| Gain S2 | J12.11 | 37 ⚠ move to J12.9 (GPIO39) |
| Gain S3 | J12.12 | 36 ⚠ move to J12.8 (GPIO40) |
| RGB LED | on module | 48 |
| Button | on module | 0 (BOOT) |

The SD lines are wired but unused by the current firmware; J5 must be an SD
**module** with its own regulator and level shifters, since it is fed +5 V on
pin 5 and the SPI lines are unbuffered.

---

## Acoustics — the conical horn

[`ultrasonic_horn_freecad.py`](ultrasonic_horn_freecad.py) is a parametric
generator for a conical horn that concentrates incoming ultrasound onto the mic
port. It is free SNR, ahead of the electronics.

| Parameter | Value |
|---|---|
| Profile | conical |
| Throat Ø (mic end) | 0.30 mm (just over the 0.25 mm mic port) |
| Mouth Ø (open end) | 28 mm (≈ 3.5 × wavelength at 45 kHz) |
| Length | 50 mm |
| Flare half-angle | ≈ 15.9° |
| Wall thickness | 0.5 mm |
| Optimised band | 40–50 kHz |
| Print | resin 25 µm (vertical), or FDM 0.12 mm / 100 % infill |

At 108 kHz the 28 mm mouth is ~8.8 wavelengths across — well above cutoff, so
the horn still delivers strong on-axis gain, just with a narrower beam that
must be aimed more precisely.

---

## Bat call levels, directivity and detection range

> Engineering **estimates** for sizing the front end — not species-accurate
> field data.

### Source levels

| Call type / example | Peak freq | SL @ 10 cm | ≈ @ 1 m | Notes |
|---|---|---|---|---|
| Loud open-air hawkers (*Nyctalus*, *Eptesicus*, *Pipistrellus*) | 25–50 kHz | 120–130 dB SPL | 100–110 dB SPL | loudest; FM/QCF sweeps |
| Horseshoe bats (*Rhinolophus*, CF) | 80–110 kHz | 105–120 dB SPL | 85–100 dB SPL | constant-frequency |
| "Whispering" gleaners (*Myotis*, *Plecotus*) | 40–90 kHz | 85–100 dB SPL | 65–80 dB SPL | very quiet, short range |

Cross-reference this against the "clips near" column in the gain table: a loud
hawker at a few metres wants the 22× or 51× step, while a distant pass wants
782×. That 31 dB spread is exactly the range v3's single fixed 625× could not
cover.

### Target species — least horseshoe bat (*Rhinolophus pusillus*)

| Parameter | Value |
|---|---|
| Call type | CF–FM (long constant-frequency tone + short FM tails) |
| Dominant CF | ≈ 106–112 kHz (~108 kHz typical) |
| Source level | moderate, ~80–90 dB SPL @ 1 m |
| FFT bin at 108 kHz | ≈ 864 (of 1024) — comfortably under the 128 kHz Nyquist |
| Est. on-axis range | **~7–9 m** (air absorption ~3.9 dB/m at this frequency) |

Consequences for the design:

- **A fast external ADC is mandatory.** At 108 kHz the call needs > 216 ksps;
  an MCU's internal ADC at 83 ksps could not see this species at all, and even
  v2's 240 ksps left it at the very edge of the band. Hence the ADCS7476 at
  256 ksps.
- **The narrowband CF tone is the easy case for the FFT detector** — its energy
  piles into one bin. Narrowing the detection window to ~100–115 kHz (bins
  ~800–920) would target this species specifically and reject the ~50 kHz USB
  noise interferer entirely.

### Directivity

| Source of directivity | Typical | Effect |
|---|---|---|
| Bat call emission | forward lobe, −3 dB half-angle ~30–40° | a bat not facing you arrives 10–20 dB weaker |
| Bare SPU0410 mic | omnidirectional | no aiming, no acoustic gain |
| With conical horn | directional lobe | +on-axis SNR/range, must be pointed |

### Estimated detection range

Loud bat, SL = 110 dB SPL @ 1 m on-axis; minimum detectable ≈ 40 dB SPL:

| Frequency | Air absorption α | Est. max range |
|---|---|---|
| 20 kHz | ~0.6 dB/m | ~60 m |
| 40 kHz | ~1.3 dB/m | ~30 m |
| 80 kHz | ~2.9 dB/m | ~16 m |
| 120 kHz | ~4.2 dB/m | ~12 m |

Optimistic ceilings — quiet bats, off-axis calls, and weather cut these
substantially.

---

## Bill of materials

Full BOM in [`v4.csv`](v4.csv), regenerated from the schematic with
`kicad-cli sch export bom`. The parts that define the design:

| Part | Qty | Role |
|---|---|---|
| SPU0410LR5H-QB | 1 | MEMS ultrasonic microphone |
| OPA838IDBVR | 1 | 1st gain stage (300 MHz GBW) |
| TL972IDR | 1 | 2nd gain / ADC driver (RRIO) |
| 74HC4053D | 1 | 3× SPDT analog mux — the gain switch |
| ADCS7476AIMFX/NOPB | 1 | 12-bit 1 MSPS SAR ADC |
| TPS74801DRCR | 1 | low-noise LDO (analog rail / VREF) |
| TP4056 | 1 | LiPo charger, 1 A |
| DW01 + FS8205A | 1 + 1 | cell protection |
| MT3608 | 1 | boost to 5.31 V |
| conical horn (`ultrasonic_horn_freecad.py`) | 1 | acoustic gain / directivity |

**Known BOM issue:** several passive symbols still carry the `Part#` and
`LCSC Part #` of their *previous* value — R13, R23/R25, R24 and R26 inherit a
24 kΩ part number, and C16 inherits a 10 nF one. Those fields are cleared in
the checked-in `v4.csv`, so ordering from it is safe, but fix the symbol
properties before the next export.

`altium_ascii_to_kicad.py` is a helper for importing Altium ASCII footprints
into the KiCad library; it is not part of the build.

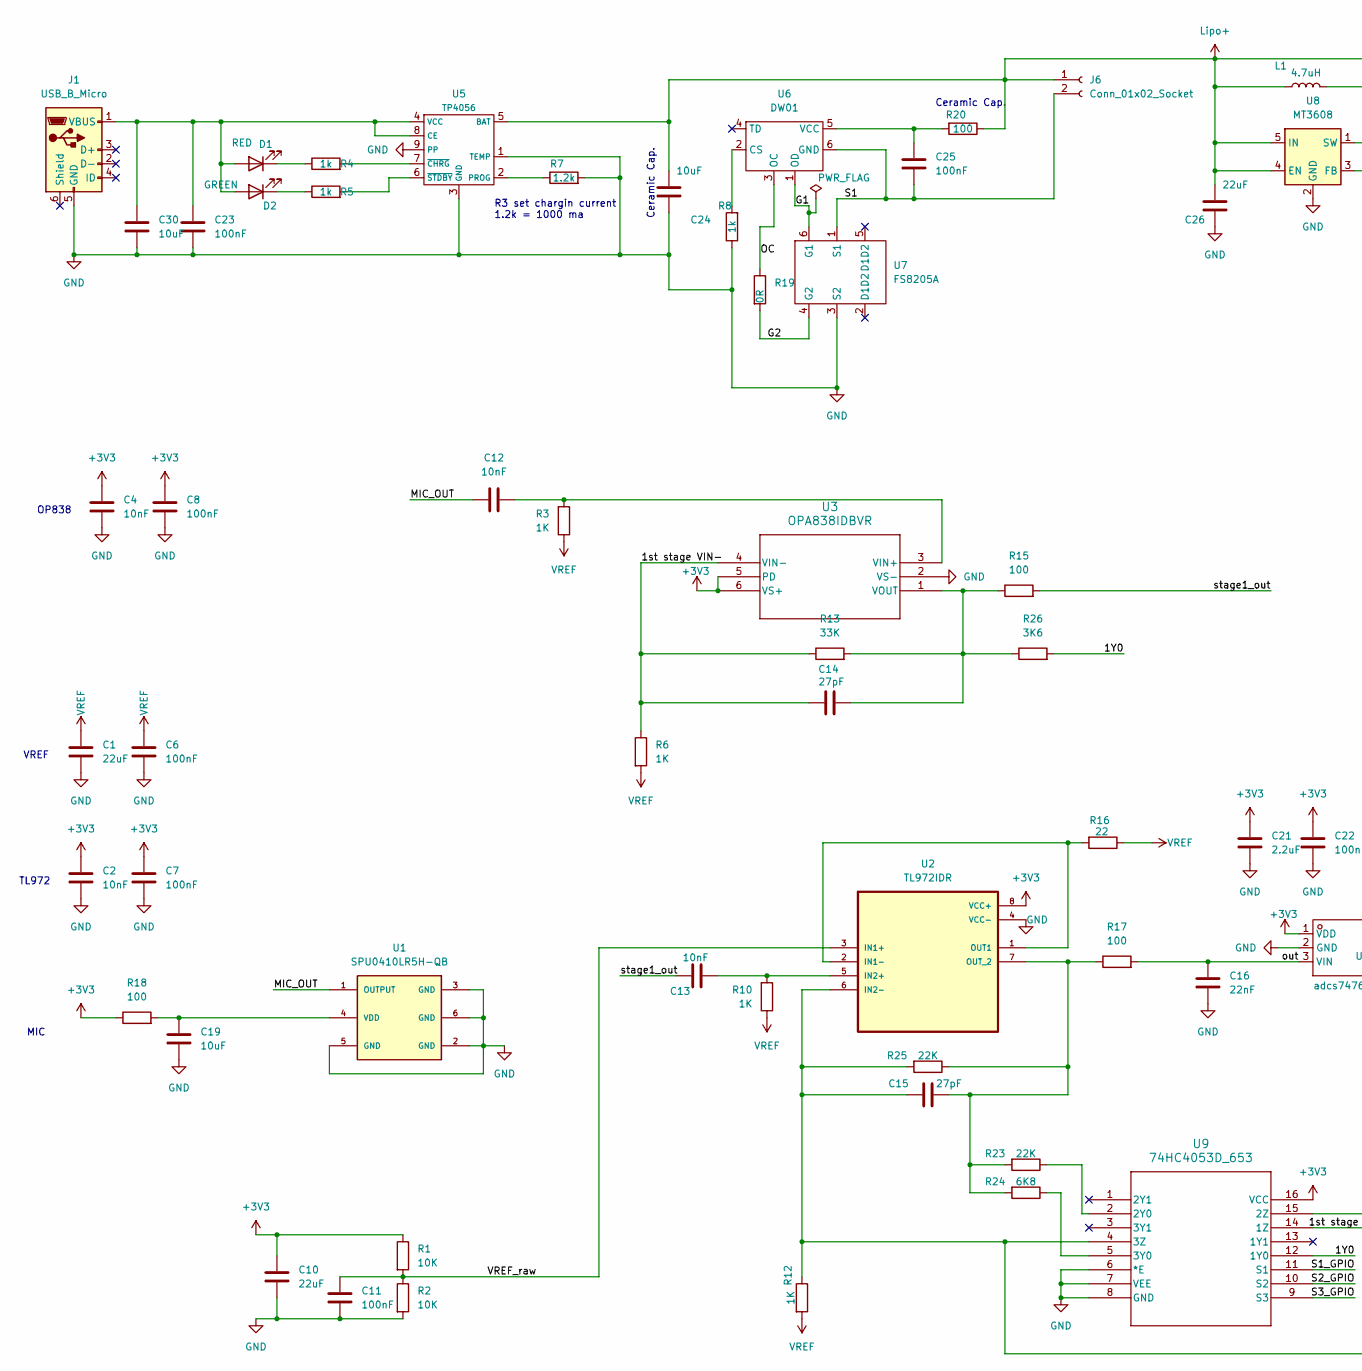
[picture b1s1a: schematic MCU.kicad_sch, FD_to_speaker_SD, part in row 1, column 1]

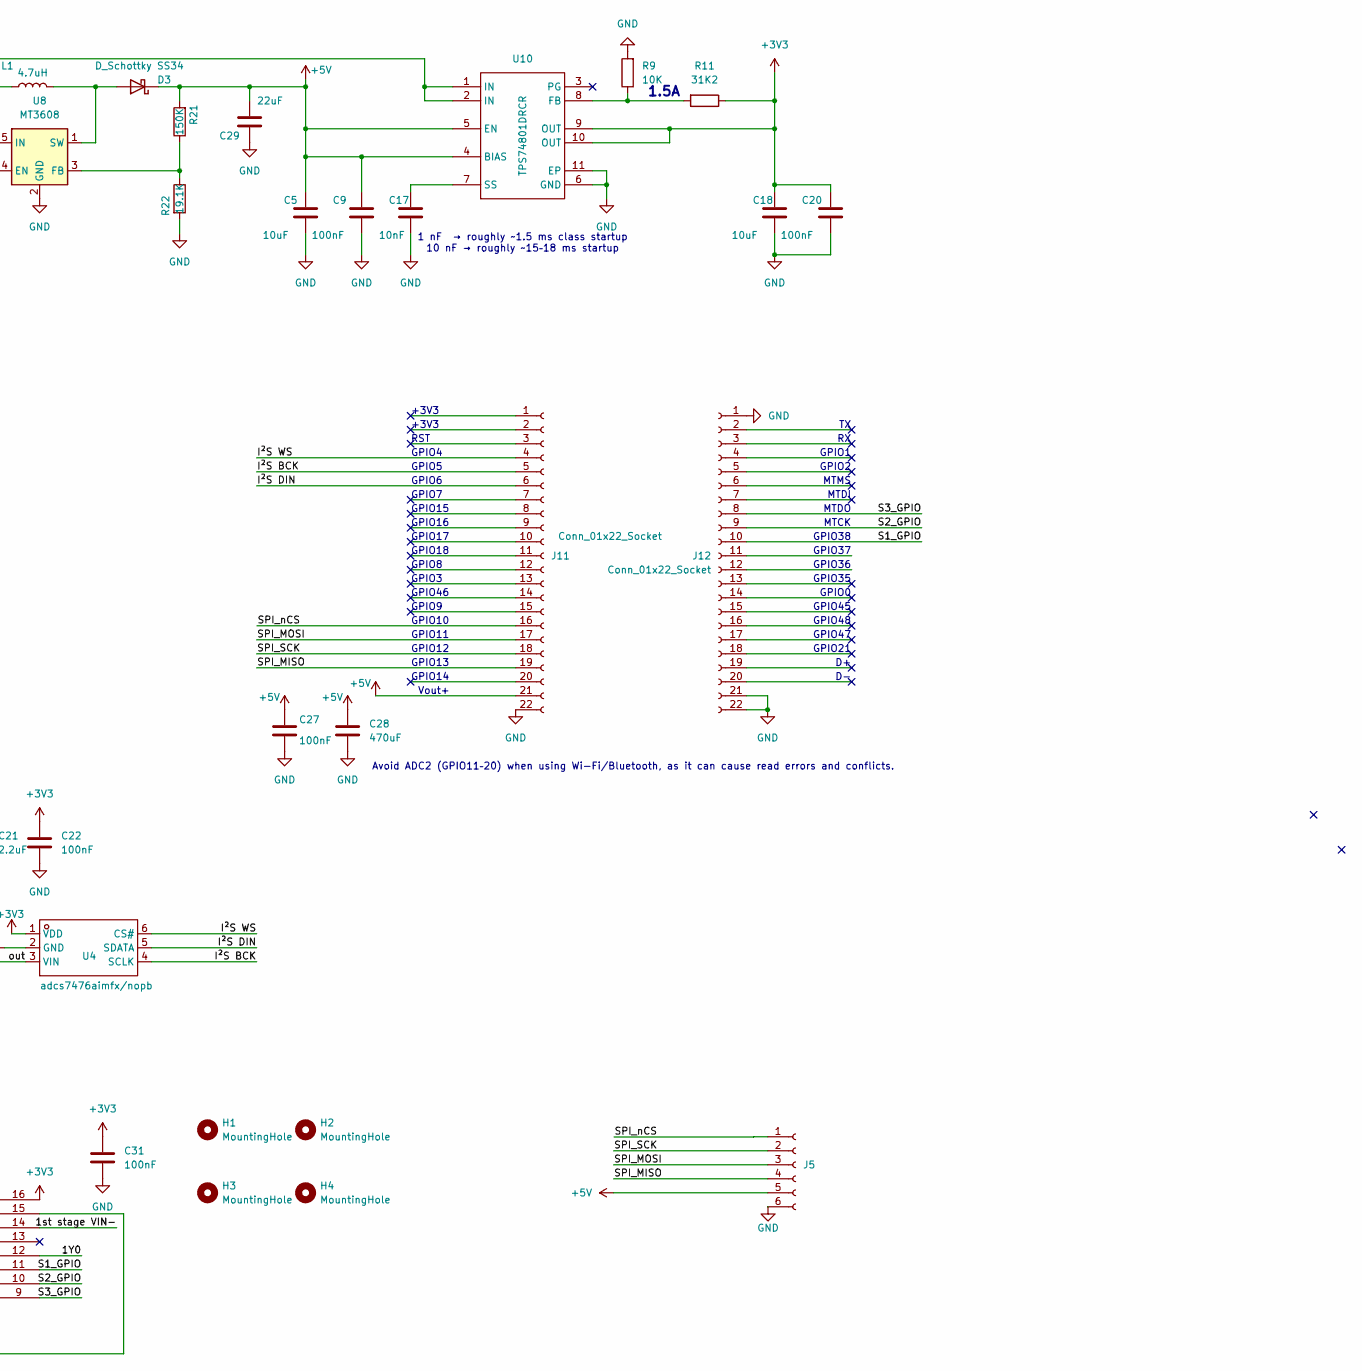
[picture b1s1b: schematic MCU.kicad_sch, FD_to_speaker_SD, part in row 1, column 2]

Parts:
C1, C10: 22uF; C_0805_2012Metric; Part# x; LCSC Part # x
C2, C4, C12, C13, C17: 10nF; C_0805_2012Metric; Part# CC0805JKNPO9BN103; LCSC Part # C527201
C5, C18: 10uF; C_0805_2012Metric; Part# x; LCSC Part # x
C6, C7, C8, C9, C11, C20, C22, C27, C31: 100nF; C_0805_2012Metric; Part# x; LCSC Part # x
C14, C15: 27pF; C_0805_2012Metric; Part# x; LCSC Part # x
C16: 22nF; C_0805_2012Metric; Part# CC0805JKNPO9BN103; LCSC Part # C527201
C19: 10uF; C_0805_2012Metric; Part# CC0805JKNPO9BN103; LCSC Part # C527201
C21: 2.2uF; C_0805_2012Metric; Part# x; LCSC Part # x
C23, C25: 100nF; C_0805_2012Metric
C24, C30: 10uF; C_0805_2012Metric
C26, C29: 22uF; C_0805_2012Metric
C28: 470uF; C_Elec_10x10.2; Part# x; LCSC Part # x
D1: RED; LED_0805_2012Metric
D2: GREEN; LED_0805_2012Metric
D3: D_Schottky SS34; D_SMA
H1, H2, H3, H4: MountingHole; MountingHole_2.1mm; Part# x; LCSC Part # x
J1: USB_B_Micro; USB_Micro-B_Molex-105017-0001
J5: Conn_01x06_Socket; PinSocket_1x06_P2.54mm_Vertical; Part# x; LCSC Part # x
J6: Conn_01x02_Socket; JST_PH_B2B-PH-K_1x02_P2.00mm_Vertical; Part# x; LCSC Part # x
J11, J12: Conn_01x22_Socket; PinSocket_1x22_P2.54mm_Vertical; Part# ZX-PM2.54-1-22PY; LCSC Part # C7499337
L1: 4.7uH; L_TechFuse_SL0420; Part# SL0420-4R7M; LCSC Part # C22463808
R1, R2, R9: 10K; R_0805_2012Metric
R3, R6, R10, R12: 1K; R_0805_2012Metric; Part# x; LCSC Part # x
R4, R5, R8: 1k; R_0805_2012Metric
R7: 1.2k; R_0805_2012Metric
R11: 31K2; R_0805_2012Metric; Part# x; LCSC Part # x
R13: 33K; R_0805_2012Metric; Part# RC0805FR-0724KL; LCSC Part # C137562
R15, R17, R18: 100; R_0805_2012Metric; Part# x; LCSC Part # x
R16: 22; R_0805_2012Metric; Part# x; LCSC Part # x
R19: 0R; R_0805_2012Metric
R20: 100; R_0805_2012Metric
R21: 150K; R_0805_2012Metric
R22: 19.1K; R_0805_2012Metric
R23: 22K; R_0805_2012Metric
R24: 6K8; R_0805_2012Metric; Part# RC0805FR-0724KL; LCSC Part # C137562
R25: 22K; R_0805_2012Metric; Part# RC0805FR-0724KL; LCSC Part # C137562
R26: 3K6; R_0805_2012Metric; Part# RC0805FR-0724KL; LCSC Part # C137562
U1: SPU0410LR5H-QB; XDCR_SPU0410LR5H-QB; Part# x; LCSC Part # x
U2: TL972IDR; SOIC-8_3.9x4.9mm_P1.27mm; Part# TL972IDR; LCSC Part # C46127
U3: OPA838IDBVR; SOT-23-6; Part# OPA838IDBVR; LCSC Part # C2058363
U4: adcs7476aimfx/nopb; SOT-23-6_Handsoldering; VOLTAGE - SUPPLY 2.7V~5.25V; VOLTAGE REFERENCE 内置; MANUFACTURERPART ADCS7476AIMFX/NOPB; LCSC PART NAME 1 Msps、12bit 、10bit 和8bit A/D转换器
U5: TP4056; SOIC-8-1EP_3.9x4.9mm_P1.27mm_EP2.29x3mm
U6: DW01; SOT-23-6
U7: FS8205A; SOT-23-6
U8: MT3608; SOT-23-6
U9: 74HC4053D_653; SO16_SOT109-1_NEX
U10: TPS74801DRCR; VSON-10-1EP_3x3mm_P0.5mm_EP1.65x2.4mm; Part# TPS74801DRCR; LCSC Part # C105263

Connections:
+3V3: C2.1, C4.1, C7.1, C8.1, C10.1, C18.1, C20.1, C21.1, C22.1, C31.1, R1.1, R11.1, R18.1, U2.8 (VCC+), U3.5 (PD), U3.6 (VS+), U4.1 (VDD), U9.16 (VCC), U10.9 (OUT), U10.10 (OUT)
+5V: C5.1, C9.1, C27.1, C28.1, C29.1, D3.1 (K), J5.5, J11.21, R21.2, U10.4 (BIAS), U10.5 (EN)
/MCU_SD/1st stage VIN-: C14.2, R6.1, R13.1, U3.4 (VIN-), U9.14 (1Z)
/MCU_SD/G1: U6.1 (OD), U7.6 (G1)
/MCU_SD/G2: R19.2, U7.4 (G2)
/MCU_SD/IY0: R26.2, U9.12 (1Y0)
/MCU_SD/I²S BCK: J11.5, U4.4 (SCLK)
/MCU_SD/I²S DIN: J11.6, U4.5 (SDATA)
/MCU_SD/I²S WS: J11.4, U4.6 (CS#)
/MCU_SD/MIC_OUT: C12.2, U1.1 (OUTPUT)
/MCU_SD/OC: R19.1, U6.3 (OC)
/MCU_SD/S1: C25.2, J6.2, U6.6 (GND), U7.1 (S1)
/MCU_SD/S1_GPIO: J12.10, U9.11 (S1)
/MCU_SD/S2_GPIO: J12.9, U9.10 (S2)
/MCU_SD/S3_GPIO: J12.8, U9.9 (S3)
/MCU_SD/SPI_MISO: J5.4, J11.19
/MCU_SD/SPI_MOSI: J5.3, J11.17
/MCU_SD/SPI_SCK: J5.2, J11.18
/MCU_SD/SPI_nCS: J5.1, J11.16
/MCU_SD/VREF_raw: C11.1, R1.2, R2.1, U2.3 (IN1+)
/MCU_SD/out: C16.1, R17.2, U4.3 (VIN)
/MCU_SD/stage1_out: C13.2, R15.2
GND: C1.2, C2.2, C4.2, C5.2, C6.2, C7.2, C8.2, C9.2, C10.2, C11.2, C16.2, C17.2, C18.2, C19.2, C20.2, C21.2, C22.2, C23.2, C24.2, C26.2, C27.2, C28.2, C29.2, C30.2, C31.2, J1.5 (GND), J5.6, J11.22, J12.1, J12.21, J12.22, R2.2, R7.2, R8.1, R9.2, R22.2, U1.2 (GND), U1.3 (GND), U1.5 (GND), U1.6 (GND), U2.4 (VCC-), U3.2 (VS-), U4.2 (GND), U5.1 (TEMP), U5.3 (GND), U5.9 (PP), U7.3 (S2), U8.2 (GND), U9.6 (*E), U9.7 (VEE), U9.8 (GND), U10.6 (GND), U10.11 (EP)
Lipo+: C24.1, C26.1, J6.1, L1.1, R20.1, U5.5 (BAT), U8.4 (EN), U8.5 (IN), U10.1 (IN), U10.2 (IN)
unnamed: C23.1, C30.1, D1.2 (A), D2.2 (A), J1.1 (VBUS), U5.4 (VCC), U5.8 (CE)
unnamed: D1.1 (K), R4.1
unnamed: D2.1 (K), R5.1
unnamed: D3.2 (A), L1.2, U8.1 (SW)
unnamed: C19.1, R18.2, U1.4 (VDD)
unnamed: R16.2, U2.1 (OUT1), U2.2 (IN1-)
unnamed: C13.1, R10.2, U2.5 (IN2+)
unnamed: C15.2, R12.1, R25.2, U2.6 (IN2-), U9.4 (3Z), U9.15 (2Z)
unnamed: C15.1, R17.1, R23.2, R24.2, R25.1, U2.7 (OUT_2)
unnamed: C12.1, R3.2, U3.3 (VIN+)
unnamed: C14.1, R13.2, R15.1, R26.1, U3.1 (VOUT)
unnamed: R7.1, U5.2 (PROG)
unnamed: R4.2, U5.7 (~CHRG)
unnamed: R5.2, U5.6 (~STDBY)
unnamed: R8.2, U6.2 (CS)
unnamed: C25.1, R20.2, U6.5 (VCC)
unnamed: R21.1, R22.1, U8.3 (FB)
unnamed: R23.1, U9.2 (2Y0)
unnamed: R24.1, U9.5 (3Y0)
unnamed: R9.1, R11.2, U10.8 (FB)
unnamed: C17.1, U10.7 (SS)
VREF: C1.1, C6.1, R3.1, R6.2, R10.1, R12.2, R16.1

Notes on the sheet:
GPIO47
GPIO5
+3V3
MTDO
GPIO2
Avoid ADC2 (GPIO11–20) when using Wi-Fi/Bluetooth, as it can cause read errors and conflicts.
MTCK
VREF
GPIO4
Ceramic Cap.
GPIO35
GPIO17
RST
GPIO6
GPIO0
GPIO10
Vout+
GPIO37
1 nF → roughly ~1.5 ms class startup 10 nF → roughly ~15–18 ms startup
GPIO9
GPIO46
GPIO11
GPIO48
TL972
MIC
MTDI
GPIO7
GPIO1
GPIO18
MTMS
GPIO13
1.5A
GPIO15
GPIO16
R3 set chargin current 1.2k = 1000 ma
GPIO12
GPIO8
GPIO36
GPIO45
GPIO14

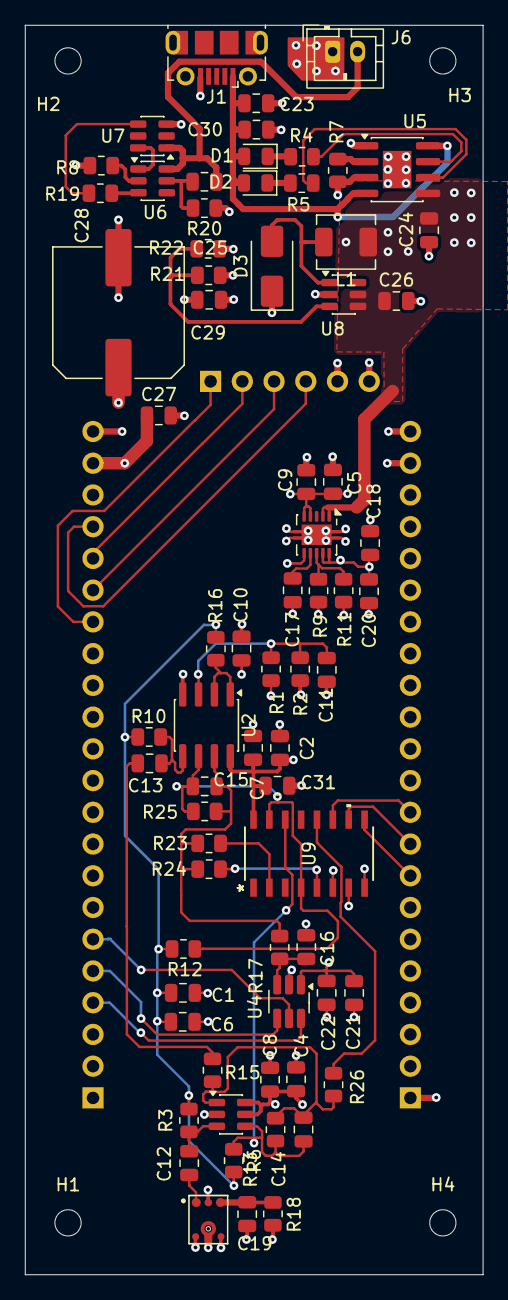
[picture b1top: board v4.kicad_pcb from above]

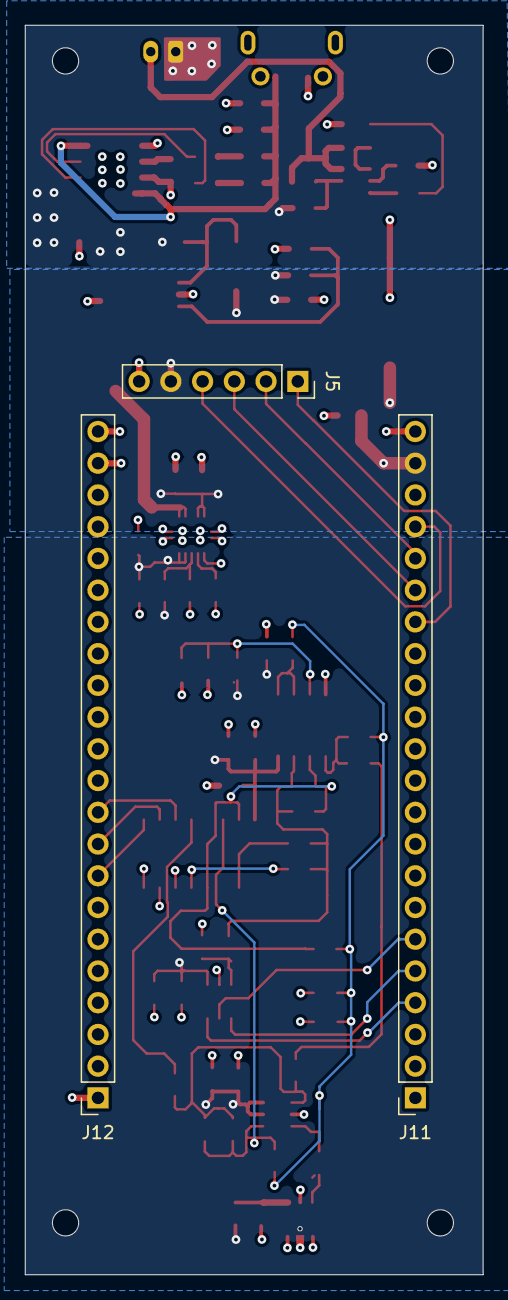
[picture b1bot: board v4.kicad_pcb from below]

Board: 4 copper layers, 36.6 x 100.0 mm, 78 parts (3 on the bottom side), 46 nets.
